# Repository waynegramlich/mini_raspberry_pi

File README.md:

# mini_raspberry_pi

Raspberry Pi Mini-Shield to bridge a Raspberry Pi to a Busino.

## Introduction

The Raspberry Pi Mini-Shield provides an
electrical bridge between a
[Busino](https://github.com/waynegramlich/busino/)
and a [Raspberry Pi](http://www.raspberrypi.org/).

## Revision A

Revision A can be found in the `rev_a` directory.  The
schematic is available as `rev_a/mini_raspberry_pi.pdf`
or `rev_a/mini_raspberry_pi.svg`.

The Rasberry Pi Mini-Shield connects to the Busino via
connectors N1 and N2.  The mini-shield connects to the
Raspberry Pi via connects N5.  Each pin on N5 is mirrored
on N4 to provide test points and alternative connection
pins for the Raspberry Pi connector.

Connector N3 is used to plug in an OKI-78SR-5/1.5-W36-C
DC-to-DC converter that converts the logic battery voltage
(VIN) coming via N2 pins 1 and 2 into 5 volts DC.  The 5V
is used to power the Raspberry Pi via N5 pins 2 and 4.

The remaining electronics is used to convert between the
Busino that is running a 5V and the Raspberry Pi that is
running at 3.3V.  Signals from the Raspberry Pi are converted
into 5 volt signals using the 74HCT123 (U1).  The signals
from the Raspberry Pi are buffered through a 74HCT08 (U2)
prior to being stepped down in voltage using a voltage
divider.

The Raspberry Pi communicates via an asynchronous serial
port.  The Raspberry Pi UART (N5 pin 8) is connect to the
Busino UART (N1 pin 1) through through a tri-state buffer
(U1C pins 8 and 9) that is always enabled (U1C pin 10).
This signal is also routed to the FTDI USB to serial
cable connector N3 (pin 5.)  Similarly, the Busino TX
signal (N1 pin 2) is sent through U2B (pins 5 and 6)
and through a 5V to 3.3V voltage divider (R1 and R2)
to the Raspberry Pi RX pin (N5 pin 10.)  In addition the
FTDI USB to serial cable connector TXD (N3 pin 4) is
also OR'ed via U2B pin 4 with Busino TX signal.  U2B
is actually an AND gate, but because the serial protocol
idles in the high state is represented in negative logic
as an OR gate with inversion circles on the inputs and
outputs.  The reason for this AND gate is because the
Raspberry Pi uses the UART as the console output.
You may plug a USB serial cable into N3 and connect to
the Raspberry Pi console using a terminal emulator.
The USB serial cable allows you to interact with the
Raspberry Pi console without have to flip a specify
where keyboard input is coming from.

The next featuret that the Raspberry_Pi Mini-Shield
support is the ability to program the Busino using
serial programming.  This is done by providing connections
from the Raspberry Pi to Busino RESET, SCLK, MISO, and
MOSI pins on N1.

RESET can be asserted from the Raspberry Pi by driving
GPIO18 (N5 pin 12) high.  This will drive the base of
transistor Q1 (pin 2)  high through the base current
limiting resistor (R5).  This will saturate Q1 and drive
RESET (N2 pin 8) low.  Please note, there is no pull-up
resistor for the collector of Q1 (pin 3) on this board
because there is a 10K pull-up resistor on the Busino.
If GPIO18 is low, there is no Q1 base current and Q1
is off, thereby leaving RESET high.  When the Raspberry
Pi reboots, GPIO18 will start off in the input state.
To prevent spurious inputs, R6 ties the base of Q1 to
ground to keep RESET from accidentally being asserted.

The SCLK and MOSI signals are driven from pins N5 (pins
19 and 23) through U1A and U1B to the corresponding pins
on N1 (pins 14 and 12).  These signals are only present
if the enable U1A and U1B enables (pins 4 and 1) are
driven low by the Raspberry Pi GPIO7 pin is driven low.
To prevent spurious enabling of these tri-state buffers,
this line is pulled up to 3.3V via resistor R7.  Lastly,
MISO is sent from N1 (pin 13) through U2A and voltage
divider R3 and R4 to the Raspberry Pi MISO pin on N5
(pin 21.)

Capacitors C1 and C2 are filter capacitors for U1 and U2.

## Random Notes

<Pre>
Parallel port:

                NC         <=> ISP 2  5V

 1 => Strobe         470K  <=> ISP 3  SCLK (D13)
 2 => D0             470K  <=> ISP 4  MOSI (D11)
 3 => D1
 4 => D2
 5 => D3
 6 => D4
 7 => D5
 8 => D6
 9 => D7
 10 <= ACK
 11 <= BUSY           220K <=> ISP 1  MISO (D12)
 12 <= PE (Paper End)
 13 <= SEL (Select)
 14 => AUTOFee
 15 <= ERROR
 16 => INIT                <=> ISP 5  #RESET
 17 => SELIN
 18-25 <=> Ground          <=> ISP 6  GND
</Pre>

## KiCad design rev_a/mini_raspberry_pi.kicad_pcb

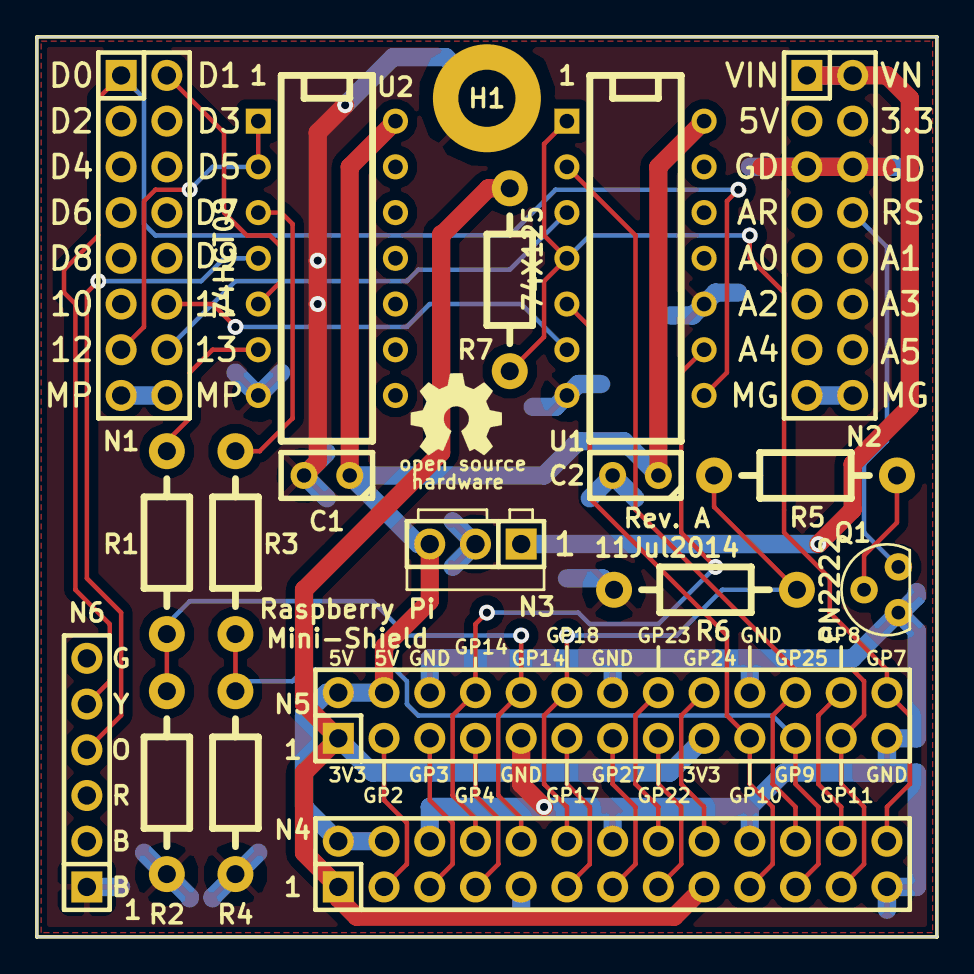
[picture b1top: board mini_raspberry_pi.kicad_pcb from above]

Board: 2 copper layers, 50.0 x 50.0 mm, 20 parts (0 on the bottom side), 33 nets.

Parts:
C1, C2: .1uF; Capacitor3MMDiscRM2.5
G1: OSHW_LOGO; OSHW_LOGO_200mil
H1: 3MM_HOLE; MountingHole_3mm
N1: MS_DATA_HEADER; Pin_Header_Straight_2x08
N2: MS_PWR_HEADER; Pin_Header_Straight_2x08
N3: OKI-78SR-5/1.5-W36-C; OKI_DC_TO_DC_CONNECTOR
N4: RASPI_CONNECTOR; Pin_Header_Straight_2x13
N5: RASPI_HEADER; Pin_Header_Straight_2x13
N6: FTDI_HEADER; Pin_Header_Straight_1x06
Q1: PN2222; TO92_123
R1, R3: 2K2 1%; Resistor_Horizontal_RM10mm
R2, R4: 3K3 1%; Resistor_Horizontal_RM10mm
R5: 470; Resistor_Horizontal_RM10mm
R6, R7: 10K; Resistor_Horizontal_RM10mm
U1: 74X125; DIP-14__300
U2: 74HCT08; DIP-14__300

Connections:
/D0: N1.1, N6.5, U1.8
/D1: N1.2, U2.5
/D11: N1.12, U1.6
/D12: N1.13, U2.1, U2.2
/D13: N1.14, U1.3
/GPIO4: N4.7, N5.7
/GPIO8: N4.24, N5.24
/GPIO17: N4.11, N5.11
/GPIO22: N4.15, N5.15
/GPIO23: N4.16, N5.16
/GPIO24: N4.18, N5.18
/GPIO25: N4.22, N5.22
/GPIO27: N4.13, N5.13
/MGND: N2.15, N2.16
/MISO_5V: R3.2, U2.3
/MPWR: N1.15, N1.16
/RP_3V3: N4.1, N4.17, N5.1, N5.17, R7.2
/RP_EN: N4.26, N5.26, R7.1, U1.1, U1.4
/RP_MISO: N4.21, N5.21, R3.1, R4.2
/RP_MOSI: N4.19, N5.19, U1.5
/RP_RST: N4.12, N5.12, R5.2, R6.2
/RP_RXD: N4.10, N5.10, R1.1, R2.2
/RP_SCL: N4.5, N5.5
/RP_SCLK: N4.23, N5.23, U1.2
/RP_SDA: N4.3, N5.3
/RP_TXD: N4.8, N5.8, U1.9
/TXD_5V: R1.2, U2.6
/VIN: N2.1, N2.2, N3.1
/~RESET: N2.8, Q1.3
GND: C1.2, C2.2, H1.1, N2.5, N2.6, N3.2, N4.6, N4.9, N4.14, N4.20, N4.25, N5.6, N5.9, N5.14, N5.20, N5.25, N6.1, Q1.1, R2.1, R4.1, R6.1, U1.7, U1.10, U2.7
unnamed: N6.4, U2.4
unnamed: Q1.2, R5.1
VCC: C1.1, C2.1, N3.3, N4.2, N4.4, N5.2, N5.4, U1.14, U2.14

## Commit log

2014-07-05 Initial copy of mini_template.
2014-07-06 Layed out PCB for Raspberry Pi Mini-Shield
2014-07-06 Fixed some broken links.
2014-07-12 Reworked to improve ground connectivity.
2014-07-13 Added edge cuts
2014-07-13 Moved a trace that was too close to PCB edge.
2014-07-13 More PCB edge incursions fixed.

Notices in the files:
rev_a/mini_raspberry_pi.kicad_pcb:
Copyright (c)
